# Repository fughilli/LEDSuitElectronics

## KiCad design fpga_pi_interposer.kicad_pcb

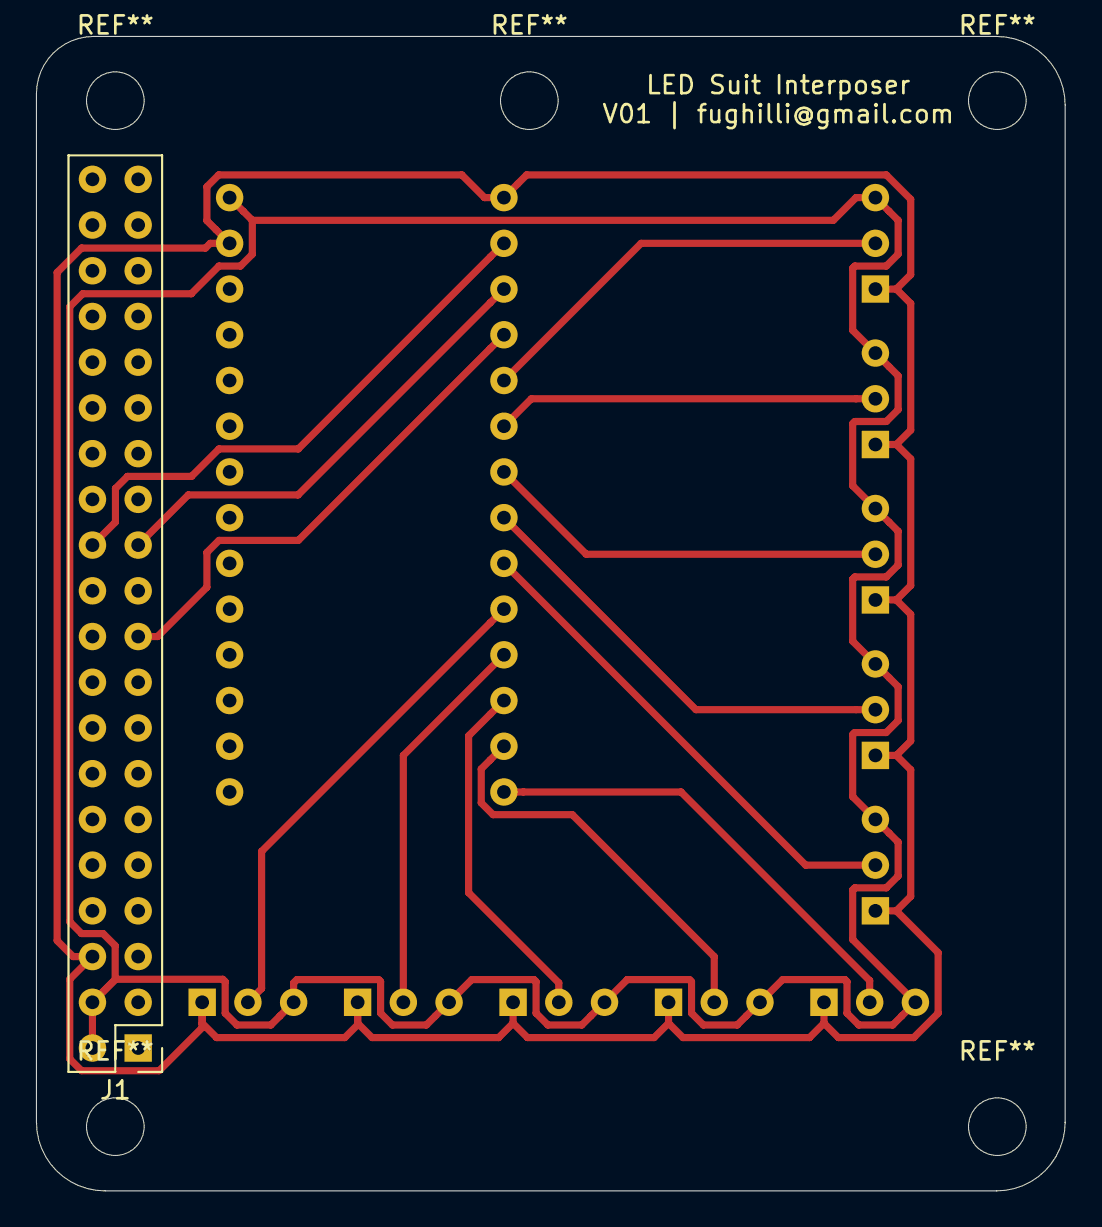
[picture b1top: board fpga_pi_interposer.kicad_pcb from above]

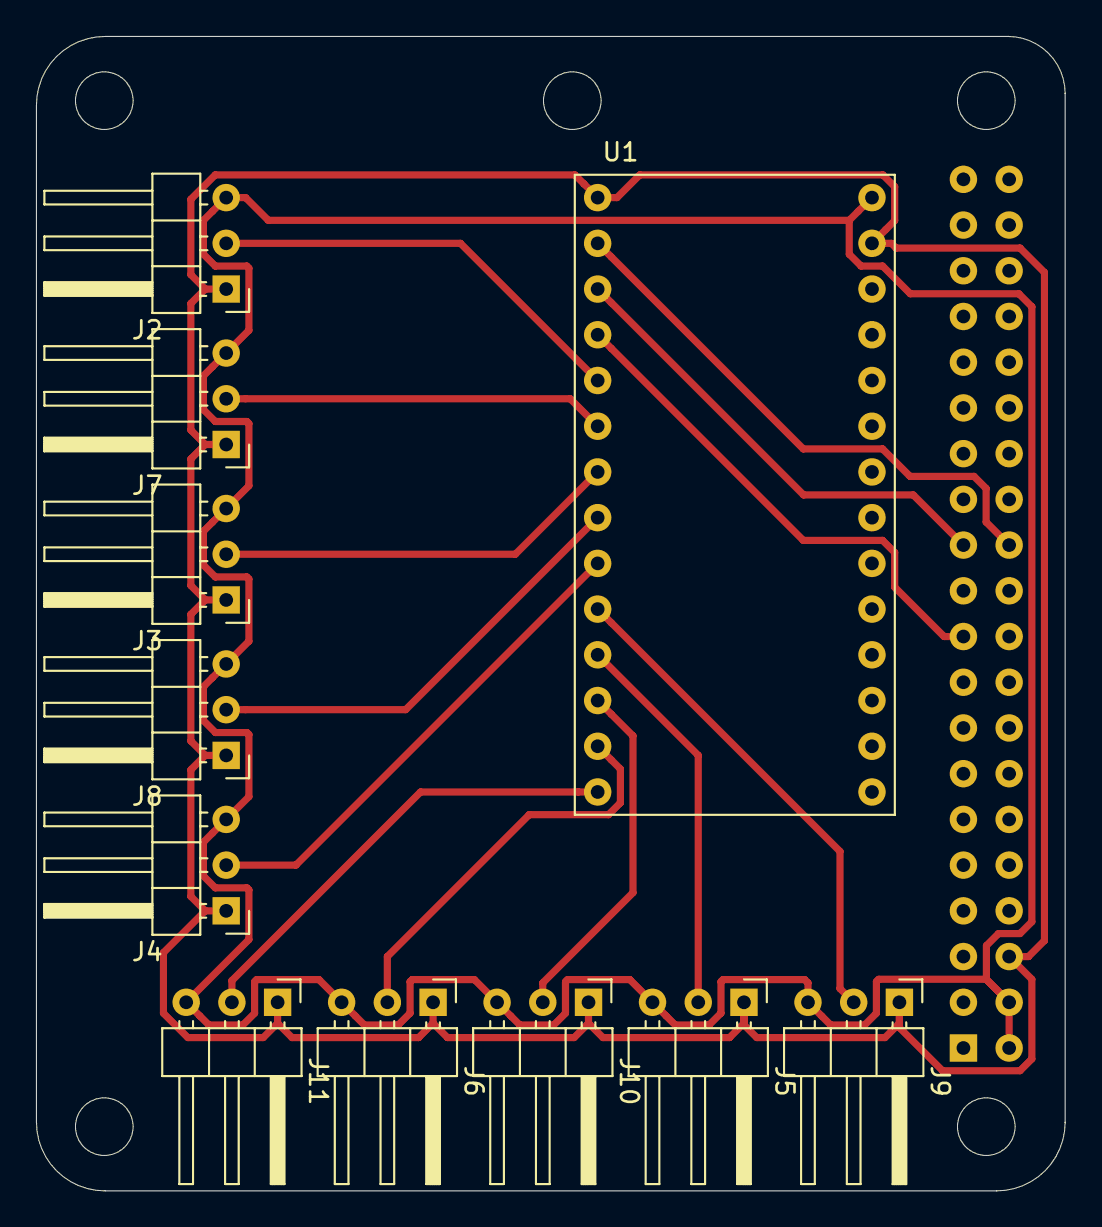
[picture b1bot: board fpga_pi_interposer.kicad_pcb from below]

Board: 2 copper layers, 57.2 x 64.1 mm, 12 parts (11 on the bottom side), 15 nets.

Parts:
J1: Conn_02x20_Odd_Even; PinHeader_2x20_P2.54mm_Vertical
J2, J3, J4, J5, J6, J7, J8, J9, J10, J11: Conn_01x03_Male; PinHeader_1x03_P2.54mm_Horizontal
U1: Tiny_FPGA_Bx; TinyFPGA_BX

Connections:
+5V: J1.2, J1.4, J2.3, J3.3, J4.3, J5.3, J6.3, J7.3, J8.3, J9.3, J10.3, J11.3, U1.28
/CS0: J1.24, U1.2
/MOSI: J1.19, U1.4
/SCK: J1.23, U1.3
/S_OUT_1: J2.2, U1.5
/S_OUT_2: J7.2, U1.6
/S_OUT_3: J3.2, U1.7
/S_OUT_4: J8.2, U1.8
/S_OUT_5: J4.2, U1.9
/S_OUT_6: J9.2, U1.10
/S_OUT_7: J5.2, U1.11
/S_OUT_8: J10.2, U1.12
/S_OUT_9: J6.2, U1.13
/S_OUT_10: J11.2, U1.14
GND: J1.6, J2.1, J3.1, J4.1, J5.1, J6.1, J7.1, J8.1, J9.1, J10.1, J11.1, U1.1, U1.27
